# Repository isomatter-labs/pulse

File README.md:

# pulse
A simple power supply / battery box / UPS for many applications.

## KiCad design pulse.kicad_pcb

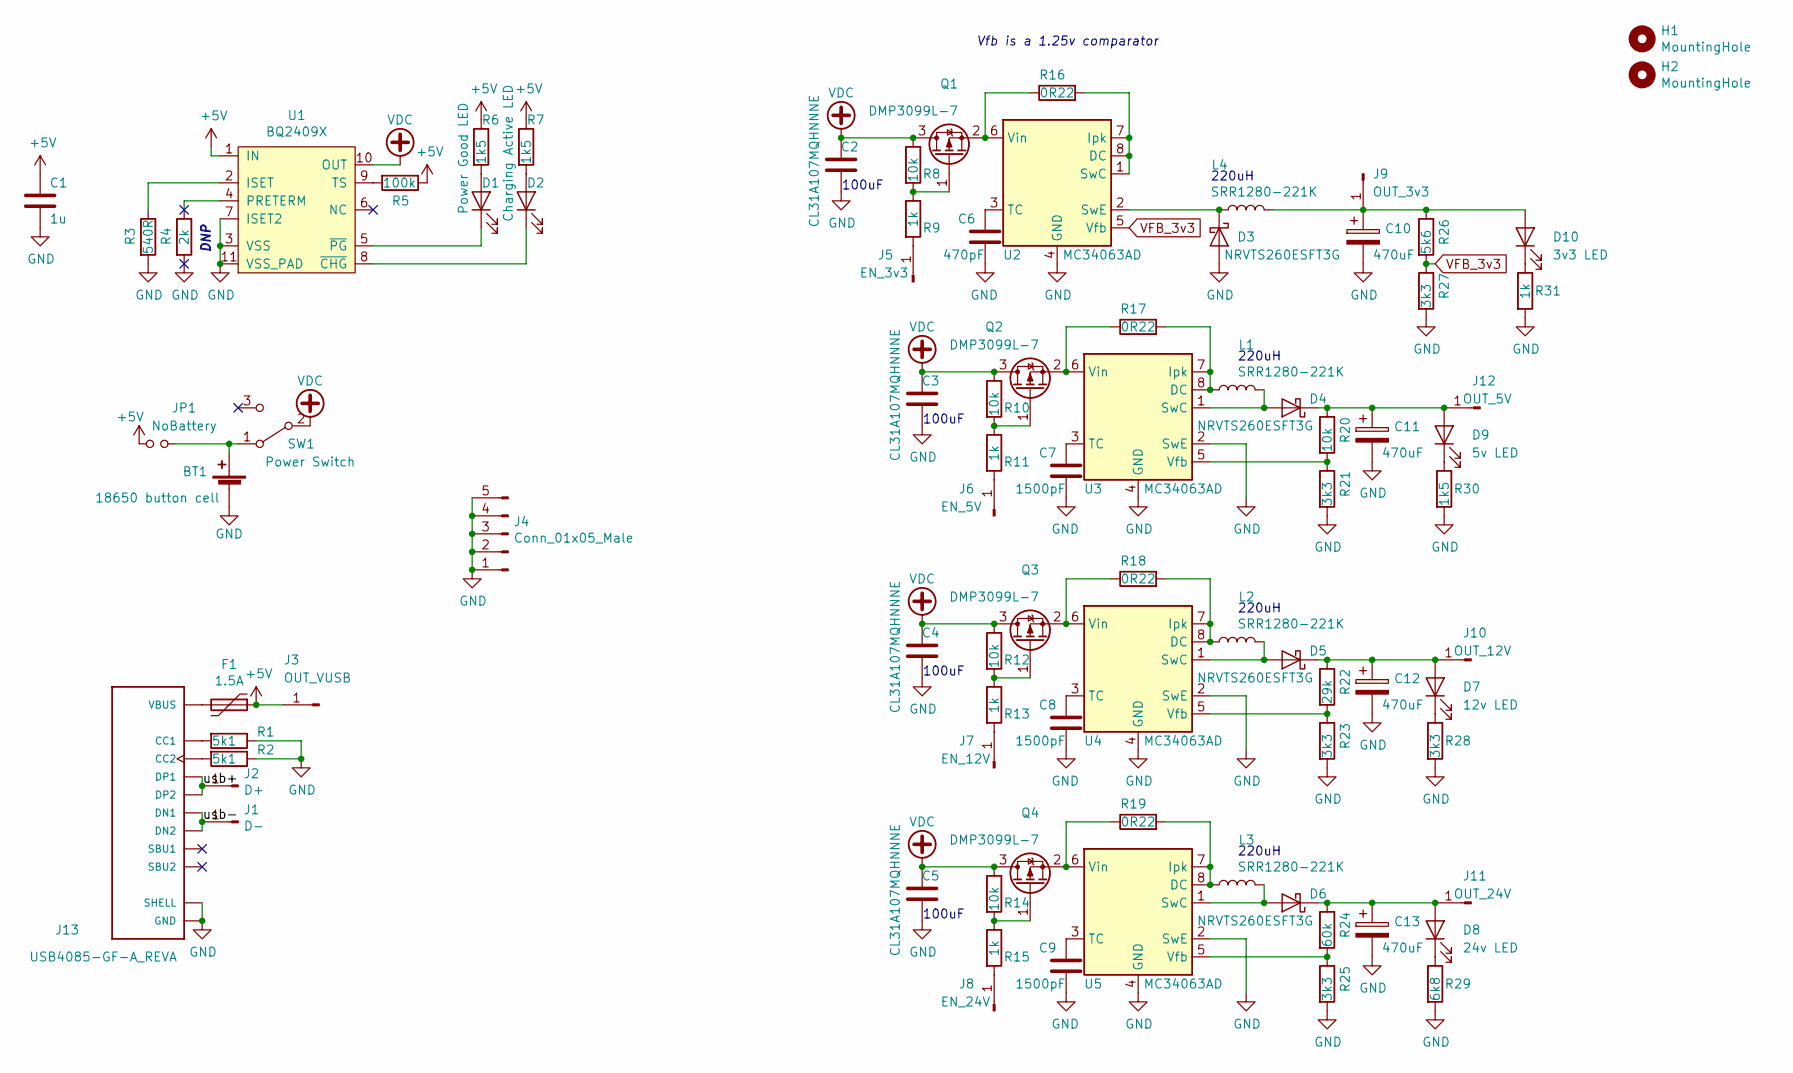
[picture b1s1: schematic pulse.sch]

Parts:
BT1: 18650 button cell; BatteryHolder_MPD_BH-18650-PC2
C1: 1u; C_0805_2012Metric
C2, C3, C4, C5: CL31A107MQHNNNE; C_1206_3216Metric
C6: 470pF; C_0805_2012Metric
C7, C8, C9: 1500pF; C_0805_2012Metric
C10, C11, C12, C13: 470uF; CP_Radial_D10.0mm_P5.00mm
D1: Power Good LED; LED_1206_3216Metric
D2: Charging Active LED; LED_1206_3216Metric
D3, D4, D5, D6: NRVTS260ESFT3G; D_SOD-123F
D7: 12v LED; LED_1206_3216Metric
D8: 24v LED; LED_1206_3216Metric
D9: 5v LED; LED_1206_3216Metric
D10: 3v3 LED; LED_1206_3216Metric
F1: 1.5A; C_0805_2012Metric
H1, H2: MountingHole; MountingHole_3.2mm_M3
J1: D-; PinHeader_1x01_P2.54mm_Vertical
J2: D+; PinHeader_1x01_P2.54mm_Vertical
J3: OUT_VUSB; PinHeader_1x01_P2.54mm_Vertical
J4: Conn_01x05_Male; PinHeader_1x05_P2.54mm_Vertical
J5: EN_3v3; PinHeader_1x01_P2.54mm_Vertical
J6: EN_5V; PinHeader_1x01_P2.54mm_Vertical
J7: EN_12V; PinHeader_1x01_P2.54mm_Vertical
J8: EN_24V; PinHeader_1x01_P2.54mm_Vertical
J9: OUT_3v3; PinHeader_1x01_P2.54mm_Vertical
J10: OUT_12V; PinHeader_1x01_P2.54mm_Vertical
J11: OUT_24V; PinHeader_1x01_P2.54mm_Vertical
J12: OUT_5V; PinHeader_1x01_P2.54mm_Vertical
J13: USB4085-GF-A_REVA; GCT_USB4085-GF-A_REVA
JP1: NoBattery; SolderJumper-2_P1.3mm_Open_Pad1.0x1.5mm
L1, L2, L3, L4: SRR1280-221K; L_Bourns_SRR1208
Q1, Q2, Q3, Q4: DMP3099L-7; SOT-23
R1, R2: 5k1; R_0805_2012Metric
R3: 540R; R_0805_2012Metric
R4: 2k; R_0805_2012Metric
R5: 100k; R_0805_2012Metric
R6, R7, R30: 1k5; R_0805_2012Metric
R8, R10, R12, R14, R20: 10k; R_0805_2012Metric
R9, R11, R13, R15, R31: 1k; R_0805_2012Metric
R16, R17, R18, R19: 0R22; R_1206_3216Metric
R21, R23, R25, R27, R28: 3k3; R_0805_2012Metric
R22: 29k; R_0805_2012Metric
R24: 60k; R_0805_2012Metric
R26: 5k6; R_0805_2012Metric
R29: 6k8; R_0805_2012Metric
SW1: Power Switch; PinHeader_1x03_P2.54mm_Vertical
U1: BQ2409X; MSOP-10-1EP_3x3mm_P0.5mm_EP1.68x1.88mm
U2, U3, U4, U5: MC34063AD; SOIC-8_3.9x4.9mm_P1.27mm

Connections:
+5V: C1.1, F1.1, J3.1, JP1.1, R5.1, R6.1, R7.1, U1.1 (IN)
/usb+: J2.1, J13.A6 (DP1), J13.B6 (DP2)
/usb-: J1.1, J13.A7 (DN1), J13.B7 (DN2)
GND: BT1.2 (-), C1.2, C2.2, C3.2, C4.2, C5.2, C6.2, C7.2, C8.2, C9.2, C10.2, C11.2, C12.2, C13.2, D3.2 (A), J4.1, J4.2, J4.3, J4.4, J4.5, J13.A1 (GND), J13.A12 (GND), J13.B1 (GND), J13.B12 (GND), J13.P1 (SHELL), J13.P2 (SHELL), J13.P3 (SHELL), J13.P4 (SHELL), R1.1, R2.1, R3.2, R4.2, R21.2, R23.2, R25.2, R27.2, R28.2, R29.2, R30.2, R31.2, U1.3 (VSS), U1.7 (ISET2), U1.11 (VSS_PAD), U2.4 (GND), U3.2 (SwE), U3.4 (GND), U4.2 (SwE), U4.4 (GND), U5.2 (SwE), U5.4 (GND)
unnamed: BT1.1 (+), JP1.2, SW1.1 (A)
unnamed: C6.1, U2.3 (TC)
unnamed: C7.1, U3.3 (TC)
unnamed: C8.1, U4.3 (TC)
unnamed: C9.1, U5.3 (TC)
unnamed: C10.1, D10.2 (A), J9.1, L4.2, R26.1
unnamed: C11.1, D4.1 (K), D9.2 (A), J12.1, R20.1
unnamed: C12.1, D5.1 (K), D7.2 (A), J10.1, R22.1
unnamed: C13.1, D6.1 (K), D8.2 (A), J11.1, R24.1
unnamed: D1.1 (K), U1.5 (~PG)
unnamed: D1.2 (A), R6.2
unnamed: D2.1 (K), U1.8 (~CHG)
unnamed: D2.2 (A), R7.2
unnamed: D3.1 (K), L4.1, U2.2 (SwE)
unnamed: D4.2 (A), L1.2, U3.1 (SwC)
unnamed: D5.2 (A), L2.2, U4.1 (SwC)
unnamed: D6.2 (A), L3.2, U5.1 (SwC)
unnamed: D7.1 (K), R28.1
unnamed: D8.1 (K), R29.1
unnamed: D9.1 (K), R30.1
unnamed: D10.1 (K), R31.1
unnamed: F1.2, J13.A4 (VBUS), J13.A9 (VBUS), J13.B4 (VBUS), J13.B9 (VBUS)
unnamed: J5.1, R9.2
unnamed: J6.1, R11.2
unnamed: J7.1, R13.2
unnamed: J8.1, R15.2
unnamed: J13.A5 (CC1), R1.2
unnamed: J13.B5 (CC2), R2.2
unnamed: L1.1, R17.2, U3.7 (Ipk), U3.8 (DC)
unnamed: L2.1, R18.2, U4.7 (Ipk), U4.8 (DC)
unnamed: L3.1, R19.2, U5.7 (Ipk), U5.8 (DC)
unnamed: Q1.1 (G), R8.2, R9.1
unnamed: Q1.2 (S), R16.1, U2.6 (Vin)
unnamed: Q2.1 (G), R10.2, R11.1
unnamed: Q2.2 (S), R17.1, U3.6 (Vin)
unnamed: Q3.1 (G), R12.2, R13.1
unnamed: Q3.2 (S), R18.1, U4.6 (Vin)
unnamed: Q4.1 (G), R14.2, R15.1
unnamed: Q4.2 (S), R19.1, U5.6 (Vin)
unnamed: R3.1, U1.2 (ISET)
unnamed: R4.1, U1.4 (PRETERM)
unnamed: R5.2, U1.9 (TS)
unnamed: R16.2, U2.1 (SwC), U2.7 (Ipk), U2.8 (DC)
unnamed: R20.2, R21.1, U3.5 (Vfb)
unnamed: R22.2, R23.1, U4.5 (Vfb)
unnamed: R24.2, R25.1, U5.5 (Vfb)
VDC: C2.1, C3.1, C4.1, C5.1, Q1.3 (D), Q2.3 (D), Q3.3 (D), Q4.3 (D), R8.1, R10.1, R12.1, R14.1, SW1.2 (B), U1.10 (OUT)
VFB_3v3: R26.2, R27.1, U2.5 (Vfb)

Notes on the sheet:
DNP
100uF
220uH
Vfb is a 1.25v comparator

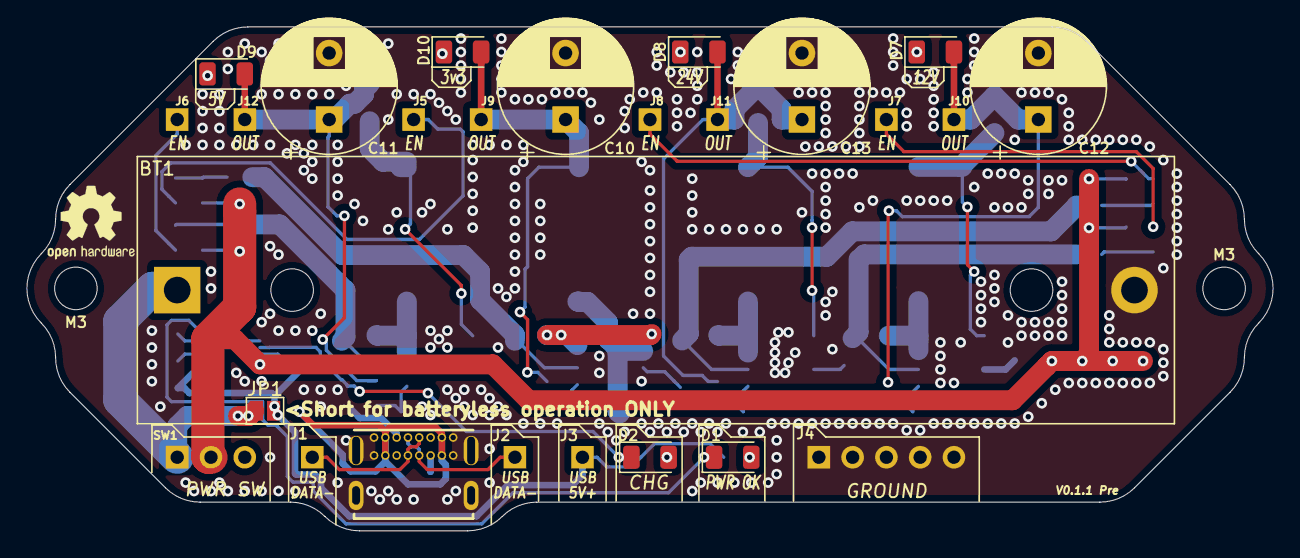
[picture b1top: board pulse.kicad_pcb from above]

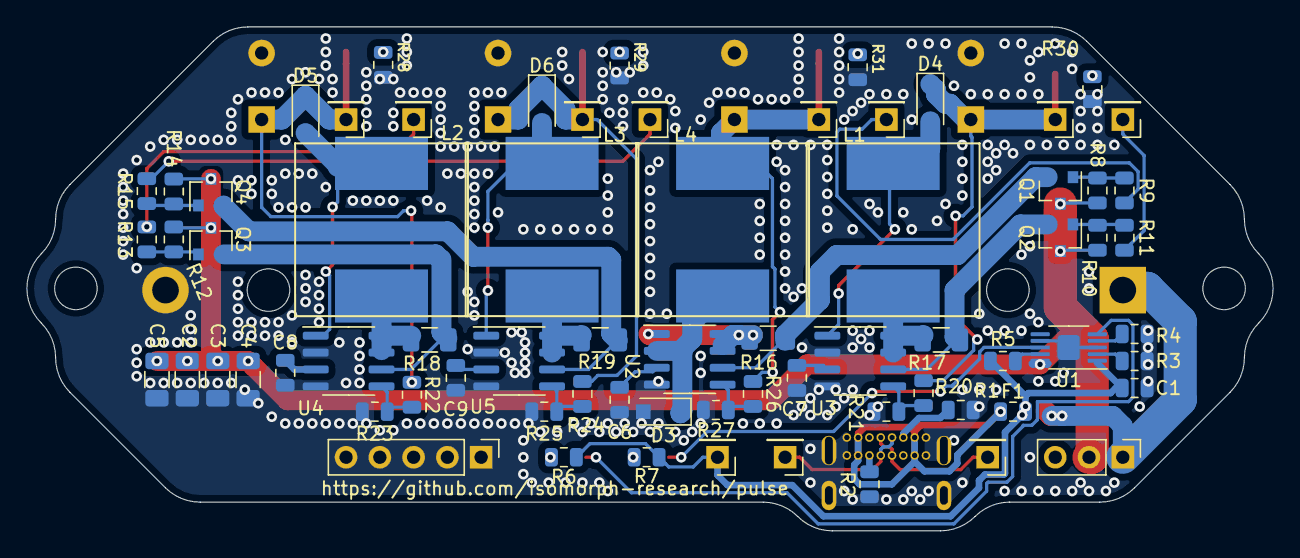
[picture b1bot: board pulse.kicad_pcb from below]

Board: 2 copper layers, 93.7 x 37.9 mm, 86 parts (71 on the bottom side), 52 nets.

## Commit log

2020-03-17 Add pre-git work
2020-03-17 Add .DS_Store to gitignore
2020-03-17 Change isomorph library line to point to local directory
2020-03-17 Fix inductor footprint and routing
2020-03-17 Fix bottom silkscreen and inductor alignment
2020-03-17 Add logos to silkscreen
2020-03-17 Fix overlapping bottom silks
2020-03-17 Export gerbers and drills for V0.0.1
2020-03-17 Change timing resistor value for 3v3 buck
2020-03-17 Add BOM doc
2020-03-18 Change PCB version Number
2020-03-18 Add batteryless operation jumper pads
2020-03-19 Change 0.22R shunt resistors to 1206
2020-03-19 Change 24vfb resistors to more common value
2020-03-19 Change 12vfb high resistor to more common value
2020-03-19 Add aliexpress alternatives for parts in BOM spreadsheet
2020-03-19 [BOM] add overhead fees to price breakdown
